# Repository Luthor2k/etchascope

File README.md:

# EtchaSkope
Supercon 2023 Badge Expansion

## Two bodge wires needed!
The high speed DAQ on the badge was the wrong choice, reroute the linear pot to the RP2040 ADC. Also need to bring 3.3V to a pull up because of a routing mistake.

### Critical Features
* badge; round LCD so polar coordinate system
  * one rotary potentiometer
  * one linear potentiometer
* mechnically attaches to supercon badge so header isn't destroyed
* red PCB incase the case doesnt print / get designed in time
* white printed/spray painted control knobs
* flip-to-erase
  * accelerometer with available micropython library
  * simple tilt switch if $$ getting $$$
* header pass through presents same mounting points / spacing for additional expansion boards

### TODO
* component selectionDONE
* pcb designDONE
* pcb submissionDONE
* enclosure designNOTHAPPENING
* print enclosures; Knobs printed last minute in white PLA by SethK, thanks Seth!
* spray knobsNOTREQ

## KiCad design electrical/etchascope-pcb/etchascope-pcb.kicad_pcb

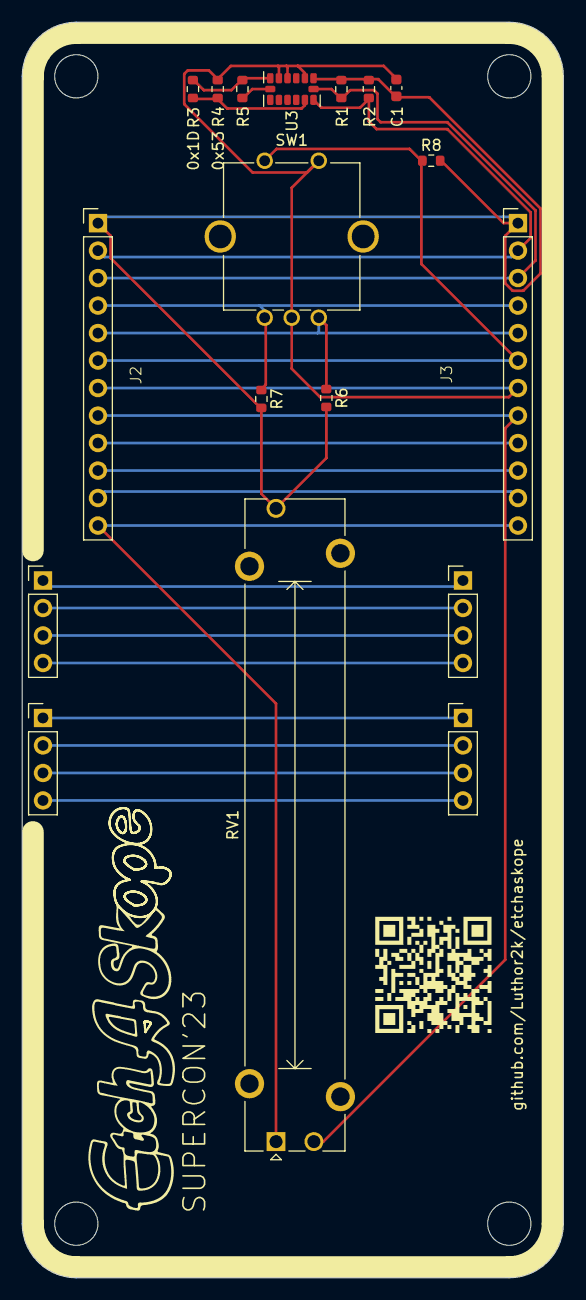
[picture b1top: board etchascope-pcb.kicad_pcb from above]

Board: 2 copper layers, 50.0 x 116.0 mm, 14 parts (0 on the bottom side), 14 nets.

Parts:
C1: 0.1; C_0603_1608Metric
J2: superconBadge23-expansion-left
J3: superconBadge23-expansion-right
R1, R2, R3, R4, R5, R6, R7, R8: 10k; R_0603_1608Metric
RV1: R_Potentiometer; Potentiometer_Bourns_PTA4543_Single_Slide
SW1: RotaryEncoder_Switch; RotaryEncoder_Bourns_Vertical_PEC12R-3xxxF-Sxxxx
U3: ADXL343; LGA-14_3x5mm_P0.8mm_LayoutBorder1x6y

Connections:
/GP26: J2.4 (GP26), J3.4 (GP26), R7.1, SW1.A
/GP27: J2.5 (GP27), J3.5 (GP27), R6.1, SW1.B
/GP28: J2.6 (GP28), J3.6 (GP28), R8.1, SW1.S1
/IN3: J2.8 (IN3), J3.8 (IN3), RV1.2
/IN4: J2.9 (IN4), J3.9 (IN4)
/OUT3: J2.10 (OUT3), J3.10 (OUT3)
/OUT4: J2.11 (OUT4), J3.11 (OUT4)
/SCL: J2.3 (SCL), J3.3 (SCL), R1.1, U3.14 (SCL/SCLK)
/SDA: J2.2 (SDA), J3.2 (SDA), R2.1, U3.13 (SDA/SDI/SDIO)
GNDA: J2.12 (AGND), J3.12 (AGND), RV1.1
GNDD: C1.2, J2.7 (DGND), J3.7 (DGND), R4.1, SW1.C, SW1.S2, U3.2 (GND), U3.4 (GND), U3.5 (GND)
unnamed: R3.1, R4.2, U3.12 (SDO/ADDR)
unnamed: R5.1, U3.7 (~CS)
VSS: C1.1, J2.1 (3V3), J3.1 (3V3), R1.2, R2.2, R3.2, R5.2, R6.2, R7.2, R8.2, RV1.3, U3.1 (Vdd_I/O), U3.6 (Vs)

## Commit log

2023-10-20 schematic underway
2023-10-20 pcb possibly complete
2023-10-20 logo added
2023-10-21 render
2023-10-21 tidied up connectors and logo
2023-10-21 tweaking logo
2023-10-21 PCBWAY submission
2023-11-03 schematic pdfs
2023-11-04 etch added to demo menu, copied from sketch, no modication done yet
2023-11-05 sketching a circle, RTOS dumped
2023-11-05 etchaskope wooooooorks!!!
2023-11-05 accelerometer working after jumping pin6 Vs to 3v3, woops!
2023-11-05 ustruct was missing
2023-11-05 bodge photos
2023-11-06 pixel size increased to 3x3, encoder speed increased 2x
